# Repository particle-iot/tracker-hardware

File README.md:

# Tracker Hardware Resources

*Hardware repository for the Tracker SoM evaluation board and carrier board (Tracker One)*

Datasheets:

- [Tracker SoM](https://docs.particle.io/datasheets/asset-tracking/tracker-som-datasheet/)
- [Tracker SoM Evaluation Board](https://docs.particle.io/datasheets/asset-tracking/tracker-som-eval-board/)
- [Tracker One](https://docs.particle.io/datasheets/asset-tracking/tracker-one/)

In this repository you can find the following directories:

- eagle-eval: The Tracker SoM evaluation board
- eagle-carrier: The Tracker carrier board (the board in the Tracker One)

Within the Eagle directories are the standard Eagle files:

- *.sch Schematic file
- *.sch.pdf PDF version of the schematic (handy if you don't have Eagle CAD)
- *.brd Board Layout file
- *.lbr Library containing all of the components in the sch/brd files
- *.rar or *.zip Gerber files
- *.cam CAM file used to produce the Gerber file

The boards are identical for both Tracker SoM versions (T402 and T523).

Other useful resources include:

- [Creating your first Tracker SoM board tutorial](https://docs.particle.io/tutorials/asset-tracking/tracker-som-first-board/).

## Version History

### Tracker One (Carrier Board) v1.1 (2020-08-18)

1. Added TS3A5018 analog switch for isolate M8 IO pins.
2. Recalculated impedance, modified RF 50 ohm and USB 90 ohm trace width.
3. Added CAN BUS 5V output bypass fuse F2.

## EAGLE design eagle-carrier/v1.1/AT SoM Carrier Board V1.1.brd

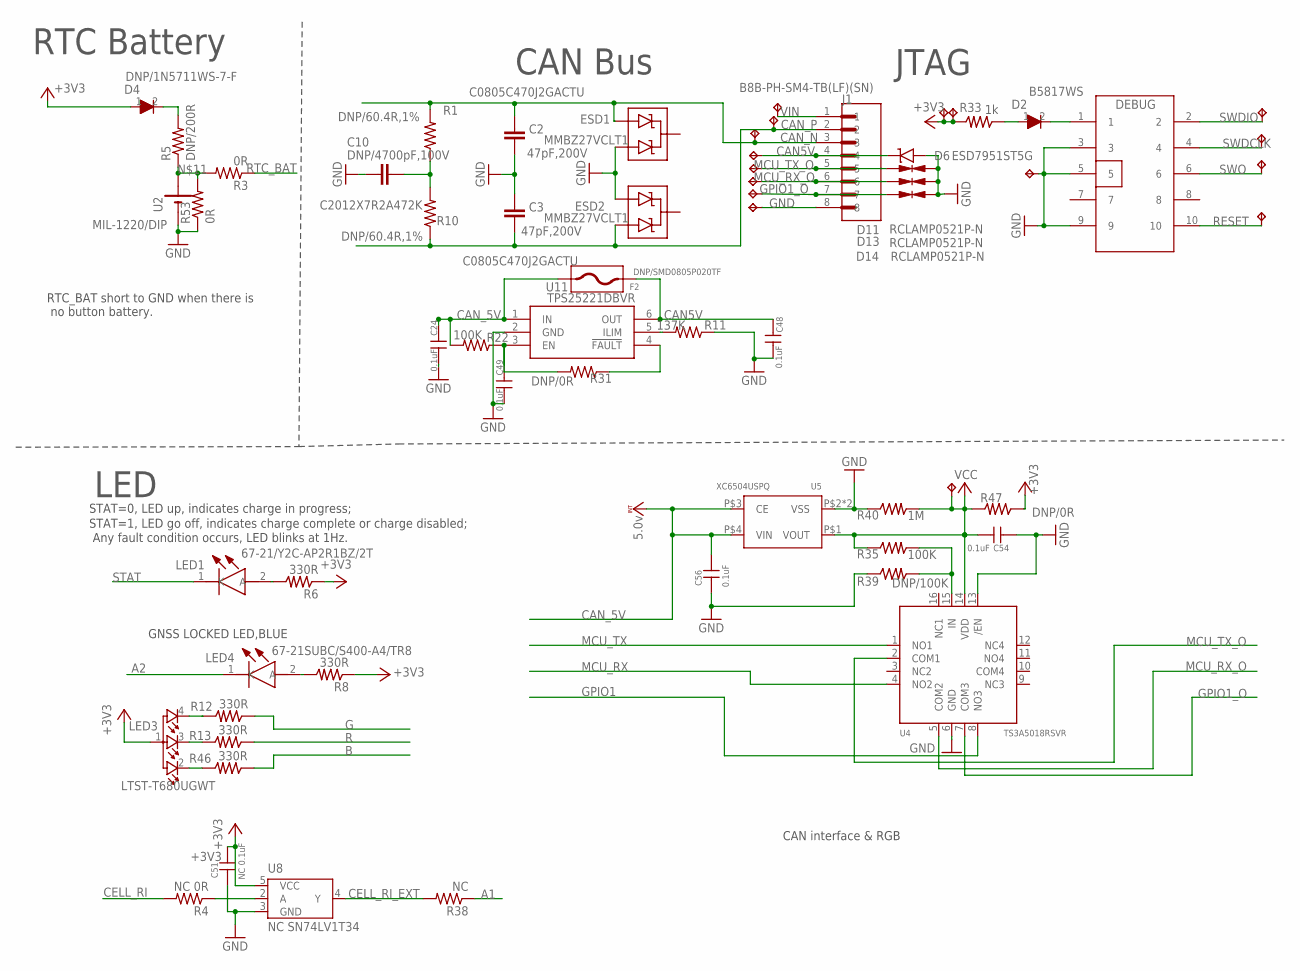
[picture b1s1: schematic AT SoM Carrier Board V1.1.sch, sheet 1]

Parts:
C2, C3: 47pF,200V; C0805; PART_NUMBER C0805C470J2GACTU
C10: DNP/4700pF,100V; C0805; PART_NUMBER C2012X7R2A472K
C24, C48, C49, C54, C56: 0.1uF; C-0402
C51: NC 0.1uF; C-0402
D2: B5817WS; SOD-323
D4: DNP/1N5711WS-7-F; SOD-323
D6: ESD7951ST5G; 0402-TVS-UNIDIR
D11, D13, D14: RCLAMP0521P-N; C0402
DEBUG: CON5X2; CON5X2_1.27
ESD1, ESD2: MMBZ27VCLT1; SOT23-3
F2: DNP/SMD0805P020TF; F0805
J1: B8B-PH-SM4-TB(LF)(SN); JST_B8B-PH-SM4-TB(LF)(SN)
LED1: 67-21/Y2C-AP2R1BZ/2T; LEDM3528X210N
LED3: LTST-T680UGWT; 150141M173100
LED4: 67-21SUBC/S400-A4/TR8; LEDM3528X210N
R1, R10: DNP/60.4R,1%; R1206
R3, R53: 0R; R0402_B
R4: NC 0R; R0402_B
R5: DNP/200R; R0402_B
R6, R8, R12, R13, R46: 330R; R-0402S
R11: 137K; R0402_B
R22: 100K; R0402_B
R31: DNP/0R; R0402_B
R33: 1k; R-0402S
R35: 100K; R-0402S
R38: NC; R0402_B
R39: DNP/100K; R-0402S
R40: 1M; R-0402S
R47: DNP/0R; R-0402S
TP11, TP12, TP13, TP15, TP16, TP21, TP22, TP43, TP44, TP46, TP47, TP48, TP49, TP50, TP51, TP52: TPTP10R; TP10R
U2: MIL-1220/DIP; BAT_ML-1220/DIP
U4: TS3A5018RSVR; UQFN-16
U5: XC6504USPQ; USPQ-4B04
U8: NC SN74LV1T34; SC70-5
U11: TPS25221DBVR; SOT95P280X145-6N

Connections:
+3V3: C51.1, D4.1, LED3.1, R6.1, R8.1, R33.2, R47.1, TP16.TP, TP21.TP, U8.5 (VCC); also elsewhere on the board
A1: R38.1; also elsewhere on the board
A2: LED4.1 (K); also elsewhere on the board
B: R46.1; also elsewhere on the board
CAN5V: C48.1, D6.1, F2.P$1 (1), J1.4, TP48.TP, U11.6 (OUT)
CAN_5V: C24.1, C56.1, F2.P$2 (2), R22.2, U5.P$3 (CE), U5.P$4 (VIN), U11.1 (IN); also elsewhere on the board
CAN_N: C2.1, ESD1.2 (A2), J1.3, R1.2, TP47.TP; also elsewhere on the board
CAN_P: C3.2, ESD2.1 (A1), J1.2, R10.1, TP46.TP; also elsewhere on the board
CELL_RI: R4.2; also elsewhere on the board
CELL_RI_EXT: R38.2, U8.4 (Y)
G: R12.1; also elsewhere on the board
GND: C2.2, C3.1, C10.1, C24.2, C48.2, C49.2, C51.2, C54.2, C56.2, D6.2, D11.2, D13.2, D14.2, DEBUG.3, DEBUG.5, DEBUG.9, ESD1.1 (A1), ESD2.2 (A2), J1.8, R11.1, R39.1, R40.1, R53.1, TP22.TP, TP52.TP, U2.1 (N), U4.6 (GND), U4.13 (/EN), U5.P$2 (VSS), U5.P$5 (VSS), U8.3 (GND), U11.2 (GND); also elsewhere on the board
GPIO1: U4.8 (NO3); also elsewhere on the board
GPIO1_O: D14.1, J1.7, TP51.TP, U4.7 (COM3)
MCU_RX: U4.4 (NO2); also elsewhere on the board
MCU_RX_O: D13.1, J1.6, TP50.TP, U4.5 (COM2)
MCU_TX: U4.1 (NO1); also elsewhere on the board
MCU_TX_O: D11.1, J1.5, TP49.TP, U4.2 (COM1)
unnamed: LED1.2 (A), R6.2
unnamed: LED4.2 (A), R8.2
unnamed: R4.1, U8.2 (A)
unnamed: D2.2, DEBUG.1
unnamed: C10.2, R1.1, R10.2
unnamed: R11.2, U11.5 (ILIM)
unnamed: R3.2, R5.1, R53.2, U2.2
unnamed: C49.1, R22.1, R31.2, U11.3 (EN)
unnamed: LED3.4, R12.2
unnamed: R31.1, U11.4 (!FAULT)
unnamed: D4.2, R5.2
unnamed: R35.2, R39.2, U4.15 (IN)
unnamed: LED3.2, R46.2
unnamed: LED3.3, R13.2
unnamed: D2.1, R33.1
R: R13.1; also elsewhere on the board
RESET: DEBUG.10, TP11.TP; also elsewhere on the board
RTC_BAT: R3.1; also elsewhere on the board
STAT: LED1.1 (K); also elsewhere on the board
SWDCLK: DEBUG.4, TP13.TP; also elsewhere on the board
SWDIO: DEBUG.2, TP15.TP; also elsewhere on the board
SWO: DEBUG.6, TP12.TP; also elsewhere on the board
VCC: C54.1, R35.1, R40.2, R47.2, TP44.TP, U4.14 (VDD), U5.P$1 (VOUT)
VIN: J1.1, TP43.TP; also elsewhere on the board

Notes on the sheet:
CAN Bus
LED
JTAG
RTC Battery
RTC_BAT short to GND when there is no button battery.
STAT=0, LED up, indicates charge in progress;
STAT=1, LED go off, indicates charge complete or charge disabled;
Any fault condition occurs, LED blinks at 1Hz.
GNSS LOCKED LED,BLUE
CAN interface & RGB

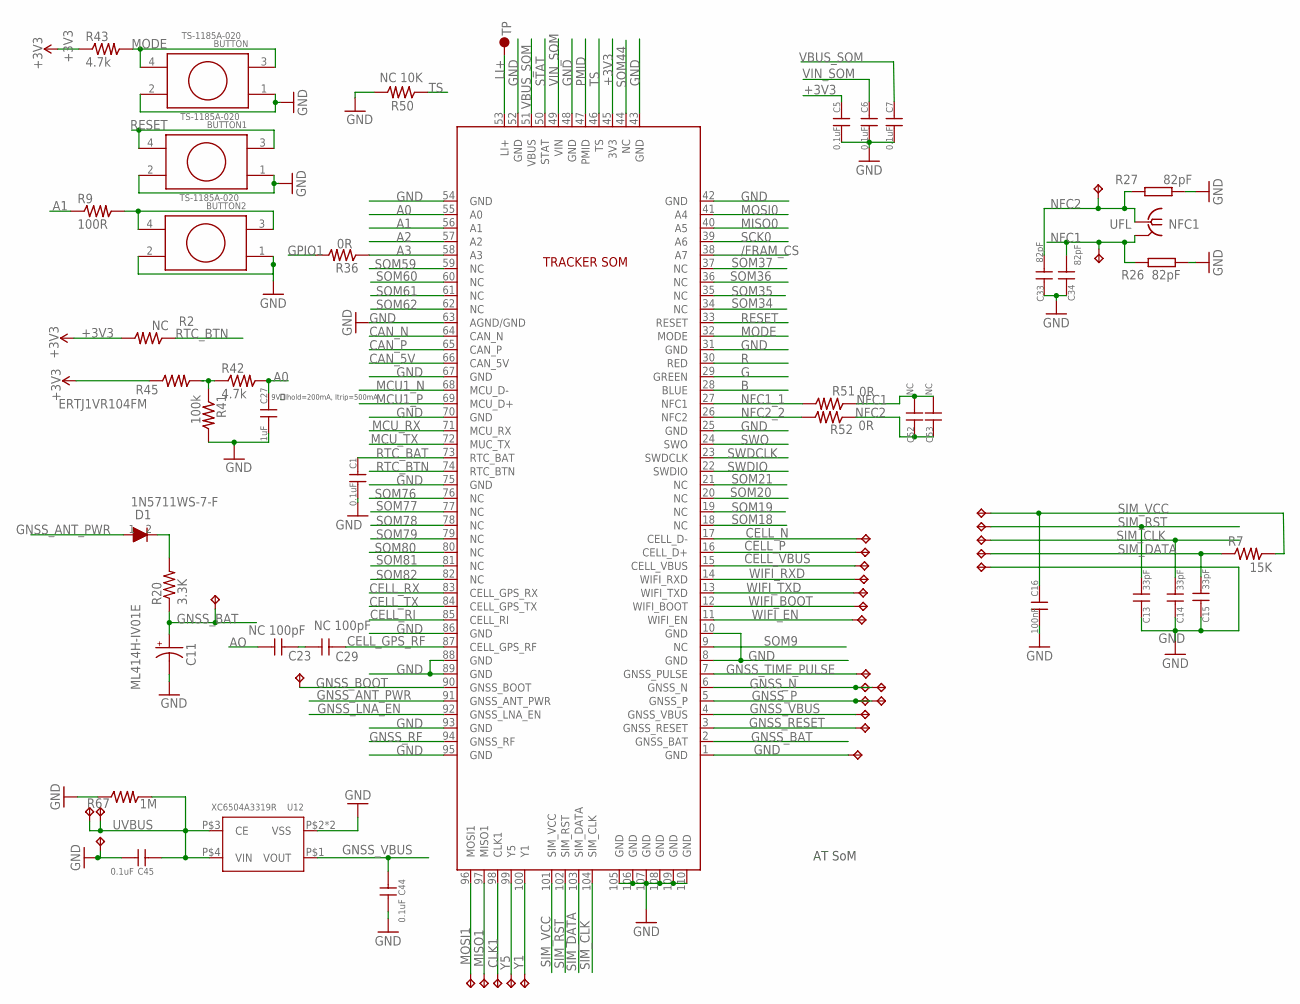
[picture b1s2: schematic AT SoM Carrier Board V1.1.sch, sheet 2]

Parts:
BUTTON, BUTTON1, BUTTON2: TS-1185A-020
C1, C5, C6, C7, C44, C45: 0.1uF; C-0402
C11: ML414H-IV01E; ML414H
C13, C14, C15: 33pF; C-0402
C16: 100nF; C-0402
C23, C29: NC 100pF; C0402_P
C27: 1uF; C-0402
C33, C34: 82pF; C-0402
C52, C53: NC; C-0402
D1: 1N5711WS-7-F; SOD-323
NFC1: UFL; IPEX-20279-001E
R2: NC; R-0402S
R7: 15K; R-0402S
R9: 100R; R-0402S
R20: 3.3K; R0603_P
R26, R27: 82pF; R-0402S
R36, R51, R52: 0R; R-0402S
R41: 100k; R-0402S
R42, R43: 4.7k; R-0402S
R45: ERTJ1VR104FM; R0603
R50: NC 10K; R-0402S
R67: 1M; R-0402S
TP1, TP2, TP3, TP4, TP5, TP6, TP7, TP8, TP9, TP14, TP17, TP18, TP19, TP20, TP27, TP28, TP29, TP30, TP31, TP32, TP33, TP34, TP35, TP36, TP37, TP38, TP39, TP40, TP41, TP42: TPTP10R; TP10R
U1: TRACKERSOM_V04
U12: XC6504A3319R; USPQ-4B04
U$1: TP2; TP70_BOT
U$9, U$10: TPTP10R; TP10R

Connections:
+3V3: C5.1, R2.2, R43.1, R45.1, U1.45 (3V3); also elsewhere on the board
/FRAM_CS: U1.38 (A7); also elsewhere on the board
A0: C27.1, R42.2, U1.55 (A0)
A1: R9.1, U1.56 (A1); also elsewhere on the board
A2: U1.57 (A2); also elsewhere on the board
A3: R36.1, U1.58 (A3)
AO: C23.1; also elsewhere on the board
B: U1.28 (BLUE); also elsewhere on the board
CAN_5V: U1.66 (CAN_5V); also elsewhere on the board
CAN_N: U1.64 (CAN_N); also elsewhere on the board
CAN_P: U1.65 (CAN_P); also elsewhere on the board
CELL_GPS_RF: C29.2, U1.87 (CELL_GPS_RF)
CELL_N: TP38.TP, U1.17 (CELL_D-)
CELL_P: TP36.TP, U1.16 (CELL_D+)
CELL_RI: U1.85 (CELL_RI); also elsewhere on the board
CELL_RX: U1.83 (CELL_GPS_RX)
CELL_TX: U1.84 (CELL_GPS_TX)
CELL_VBUS: TP35.TP, U1.15 (CELL_VBUS)
CLK1: TP40.TP, U1.98 (CLK1)
G: U1.29 (GREEN); also elsewhere on the board
GND: BUTTON.1, BUTTON.2, BUTTON1.1, BUTTON1.2, BUTTON2.1, BUTTON2.2, C1.2, C5.2, C6.2, C7.2, C11.-, C13.1, C14.1, C15.1, C16.2, C27.2, C33.1, C34.1, C44.1, C45.1, R26.2, R27.1, R41.2, R50.2, R67.1, TP18.TP, TP20.TP, TP32.TP, U1.1 (GND), U1.8 (GND), U1.10 (GND), U1.25 (GND), U1.31 (GND), U1.42 (GND), U1.43 (GND), U1.48 (GND), U1.52 (GND), U1.54 (GND), U1.63 (AGND/GND), U1.67 (GND), U1.70 (GND), U1.75 (GND), U1.86 (GND), U1.88 (GND), U1.89 (GND), U1.93 (GND), U1.95 (GND), U1.105 (GND), U1.106 (GND), U1.107 (GND), U1.108 (GND), U1.109 (GND), U1.110 (GND), U12.P$2 (VSS), U12.P$5 (VSS); also elsewhere on the board
GNSS_ANT_PWR: D1.1, U1.91 (GNSS_ANT_PWR); also elsewhere on the board
GNSS_BAT: C11.+, R20.1, TP9.TP, U1.2 (GNSS_BAT)
GNSS_BOOT: TP6.TP, U1.90 (GNSS_BOOT)
GNSS_LNA_EN: U1.92 (GNSS_LNA_EN); also elsewhere on the board
GNSS_N: TP14.TP, TP34.TP, U1.6 (GNSS_N); also elsewhere on the board
GNSS_P: TP5.TP, TP19.TP, U1.5 (GNSS_P); also elsewhere on the board
GNSS_RESET: TP8.TP, U1.3 (GNSS_RESET)
GNSS_RF: U1.94 (GNSS_RF); also elsewhere on the board
GNSS_TIME_PULSE: TP7.TP, U1.7 (GNSS_PULSE)
GNSS_VBUS: C44.2, TP30.TP, U1.4 (GNSS_VBUS), U12.P$1 (VOUT)
GPIO1: R36.2; also elsewhere on the board
LI+: U1.53 (LI+), U$1.P$1; also elsewhere on the board
MCU1_N: U1.68 (MCU_D-); also elsewhere on the board
MCU1_P: U1.69 (MCU_D+); also elsewhere on the board
MCU_RX: U1.71 (MCU_RX); also elsewhere on the board
MCU_TX: U1.72 (MUC_TX); also elsewhere on the board
MISO0: U1.40 (A5); also elsewhere on the board
MISO1: TP39.TP, U1.97 (MISO1)
MODE: BUTTON.3, BUTTON.4, R43.2, U1.32 (MODE)
MOSI0: U1.41 (A4); also elsewhere on the board
MOSI1: TP37.TP, U1.96 (MOSI1)
unnamed: R41.1, R42.1, R45.2
unnamed: D1.2, R20.2
unnamed: C23.2, C29.1
unnamed: BUTTON2.3, BUTTON2.4, R9.2
NFC1: C34.2, C52.2, C53.2, NFC1.2@1 (GND), NFC1.2@2 (GND), R26.1, R51.1, U$10.TP
NFC1_1: R51.2, U1.27 (NFC1)
NFC2: C33.2, C52.1, C53.1, NFC1.1, R27.2, R52.1, U$9.TP
NFC2_2: R52.2, U1.26 (NFC2)
PMID: U1.47 (PMID)
R: U1.30 (RED); also elsewhere on the board
RESET: BUTTON1.3, BUTTON1.4, U1.33 (RESET); also elsewhere on the board
RTC_BAT: C1.1, U1.73 (RTC_BAT); also elsewhere on the board
RTC_BTN: R2.1, U1.74 (RTC_BTN)
SCK0: U1.39 (A6); also elsewhere on the board
SIM_CLK: C14.2, TP29.TP, U1.104 (SIM_CLK)
SIM_DATA: C15.2, R7.1, TP31.TP, U1.103 (SIM_DATA)
SIM_RST: C13.2, TP28.TP, U1.102 (SIM_RST)
SIM_VCC: C16.1, R7.2, TP27.TP, U1.101 (SIM_VCC)
SOM9: U1.9 (NC)
SOM18: U1.18 (NC)
SOM19: U1.19 (NC)
SOM20: U1.20 (NC)
SOM21: U1.21 (NC)
SOM34: U1.34 (NC)
SOM35: U1.35 (NC)
SOM36: U1.36 (NC)
SOM37: U1.37 (NC)
SOM44: U1.44 (NC)
SOM59: U1.59 (NC)
SOM60: U1.60 (NC)
SOM61: U1.61 (NC)
SOM62: U1.62 (NC)
SOM76: U1.76 (NC)
SOM77: U1.77 (NC)
SOM78: U1.78 (NC)
SOM79: U1.79 (NC)
SOM80: U1.80 (NC)
SOM81: U1.81 (NC)
SOM82: U1.82 (NC)
STAT: U1.50 (STAT); also elsewhere on the board
SWDCLK: U1.23 (SWDCLK); also elsewhere on the board
SWDIO: U1.22 (SWDIO); also elsewhere on the board
SWO: U1.24 (SWO); also elsewhere on the board
TS: R50.1, U1.46 (TS)
UVBUS: C45.2, R67.2, TP17.TP, TP33.TP, U12.P$3 (CE), U12.P$4 (VIN); also elsewhere on the board
VBUS_SOM: C7.1, U1.51 (VBUS); also elsewhere on the board
VIN_SOM: C6.1, U1.49 (VIN); also elsewhere on the board
WIFI_BOOT: TP3.TP, U1.12 (WIFI_BOOT)
WIFI_EN: TP4.TP, U1.11 (WIFI_EN)
WIFI_RXD: TP1.TP, U1.14 (WIFI_RXD)
WIFI_TXD: TP2.TP, U1.13 (WIFI_TXD)
Y1: TP42.TP, U1.100 (Y1)
Y5: TP41.TP, U1.99 (Y5)

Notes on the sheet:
AT SoM
9V，Ihold=200mA, Itrip=500mA

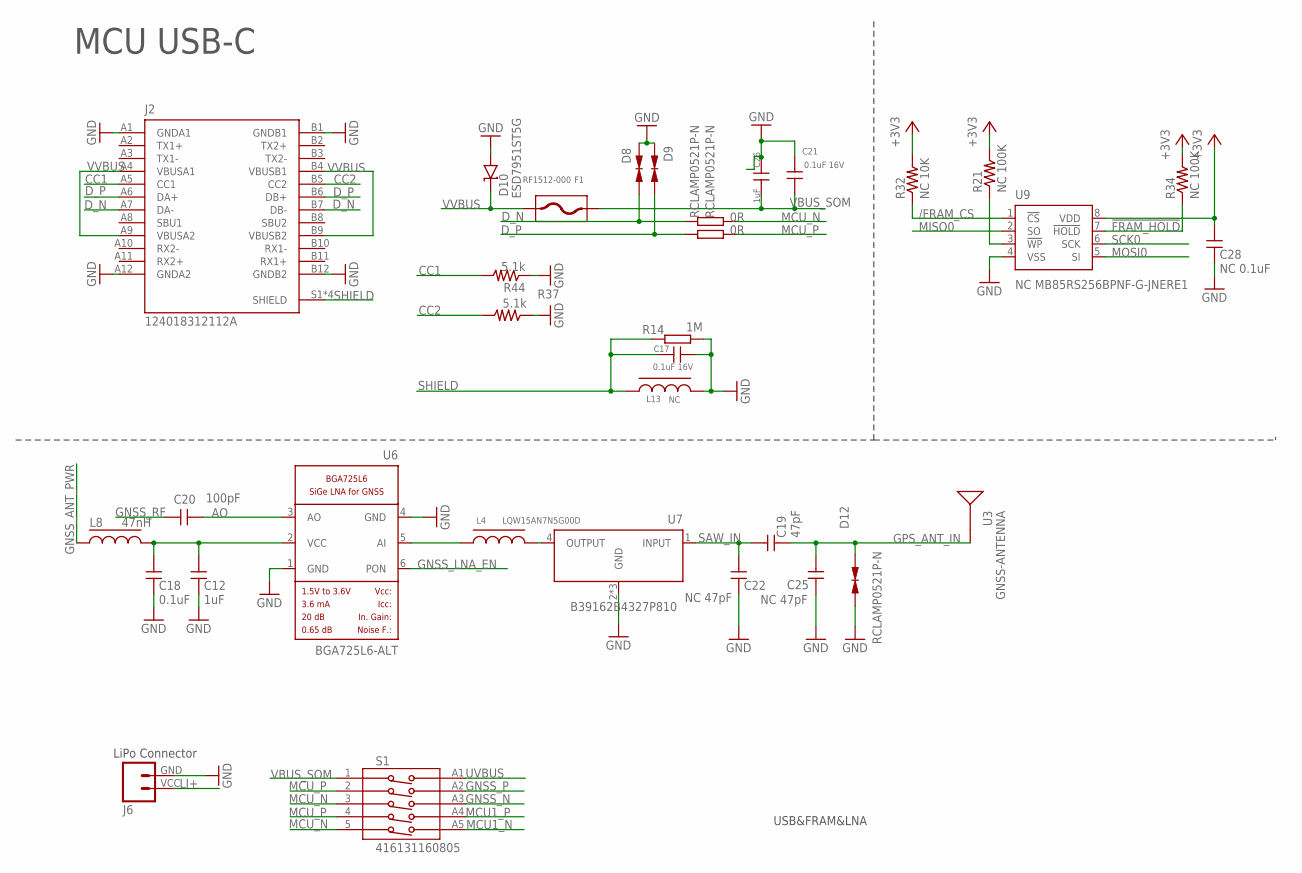
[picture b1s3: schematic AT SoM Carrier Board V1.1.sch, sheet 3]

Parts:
C12: 1uF; C0402_P
C17: 0.1uF 16V; PARTICLE-SZ_C-0402
C18: 0.1uF; C0402_P
C19: 47pF; C0402_P
C20: 100pF; C0402_P
C21: 0.1uF 16V; C-0402
C22, C25: NC 47pF; C0402_P
C26: 1uF; C-0402
C28: NC 0.1uF; C0402_P
D8, D9, D12: RCLAMP0521P-N; C0402
D10: ESD7951ST5G; 0402-TVS-UNIDIR
F1: RF1512-000; R1206
J2: 124018312112A; AMPHENOL_124018312112A
J6: M024UCON-15767; JST-2-SMD-VERT
L4: LQW15AN7N5G00D; R-0402S
L8: 47nH; R-0402S
L13: NC; R-0603A
R14: 1M; REDBEAR_R0603
R15, R16: 0R; R-0402S
R21, R34: NC 100K; R-0402S
R32: NC 10K; R-0402S
R37, R44: 5.1k; R-0402S
S1: 416131160805
U3: GNSS-ANTENNA; PA035AZ0004
U6: BGA725L6-ALT; LNA-TSLP-6-2-ALT
U7: B39162B4327P810; QCS5I
U9: NC MB85RS256BPNF-G-JNERE1; SO08

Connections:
!FRAM_HOLD: R34.1, U9.7 (!HOLD)
!FRAM_WP: R21.1, U9.3 (!WP)
+3V3: C28.1, R21.2, R32.2, R34.2, U9.8 (VDD); also elsewhere on the board
/FRAM_CS: R32.1, U9.1 (!CS); also elsewhere on the board
AO: C20.2, U6.3 (AO); also elsewhere on the board
CC1: J2.A5 (CC1), R44.2
CC2: J2.B5 (CC2), R37.2
D_N: D8.2, J2.A7 (DA-), J2.B7 (DB-), R15.1
D_P: D9.2, J2.A6 (DA+), J2.B6 (DB+), R16.1
GND: C12.2, C17.2, C18.2, C21.2, C22.2, C25.1, C26.1, C28.2, D8.1, D9.1, D10.2, D12.2, J2.A1 (GNDA1), J2.A12 (GNDA2), J2.B1 (GNDB1), J2.B12 (GNDB2), J6.GND (1), L13.2, R14.2, R37.1, R44.1, U6.1 (GND), U6.4 (GND), U7.2 (GND), U7.3 (GND), U7.5 (GND), U9.4 (VSS); also elsewhere on the board
GNSS_ANT_PWR: L8.1; also elsewhere on the board
GNSS_LNA_EN: U6.6 (PON); also elsewhere on the board
GNSS_N: S1.A3; also elsewhere on the board
GNSS_P: S1.A2; also elsewhere on the board
GNSS_RF: C20.1; also elsewhere on the board
GPS_ANT_IN: C19.2, C25.2, D12.1, U3.P$1
LI+: J6.VCC (2); also elsewhere on the board
MCU1_N: S1.A5; also elsewhere on the board
MCU1_P: S1.A4; also elsewhere on the board
MCU_N: R15.2, S1.3, S1.5
MCU_P: R16.2, S1.2, S1.4
MISO0: U9.2 (SO); also elsewhere on the board
MOSI0: U9.5 (SI); also elsewhere on the board
unnamed: L4.2, U7.4 (OUTPUT)
unnamed: L4.1, U6.5 (AI)
unnamed: C12.1, C18.1, L8.2, U6.2 (VCC)
SAW_IN: C19.1, C22.1, U7.1 (INPUT)
SCK0: U9.6 (SCK); also elsewhere on the board
SHIELD: C17.1, J2.S1 (SHIELD), J2.S2 (SHIELD), J2.S3 (SHIELD), J2.S4 (SHIELD), L13.1, R14.1
UVBUS: S1.A1; also elsewhere on the board
VBUS_SOM: C21.1, C26.2, F1.2, S1.1; also elsewhere on the board
VVBUS: D10.1, F1.1, J2.A4 (VBUSA1), J2.A9 (VBUSA2), J2.B4 (VBUSB1), J2.B9 (VBUSB2)

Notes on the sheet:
MCU USB-C
USB&FRAM&LNA
LiPo Connector

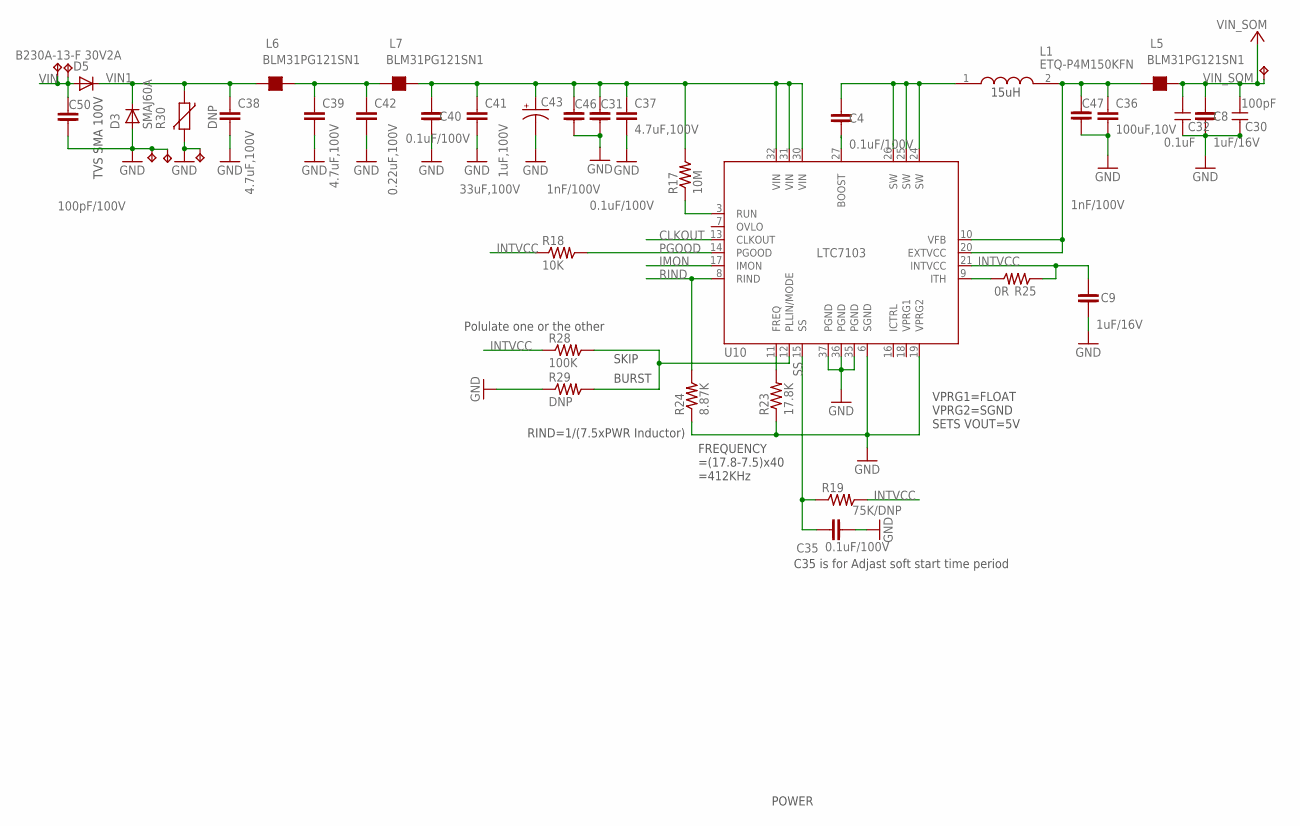
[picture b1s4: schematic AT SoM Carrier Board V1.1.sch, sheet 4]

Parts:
C4, C31, C35, C40: 0.1uF/100V; C-0603A
C8, C9: 1uF/16V; C-0402
C30: 100pF; C0402_P
C32: 0.1uF; C0402_P
C36: 100uF,10V; C1210
C37, C38, C39: 4.7uF,100V; C1210
C41: 1uF,100V; C0805
C42: 0.22uF,100V; C0805
C43: 33uF,100V; NIC_10X10.5_CAP
C46, C47: 1nF/100V; C-0603A
C50: 100pF/100V; C-0603A
D3: SMAJ60A; SMADIODE
D5: B230A-13-F 30V2A; SMADIODE
L1: ETQ-P4M150KFN; ETQP4M150KFN
L5, L6, L7: BLM31PG121SN1; L1206
R17: 10M; R-0402S
R18: 10K; R-0402S
R19: 75K/DNP; R-0402S
R23: 17.8K; R0603_P
R24: 8.87K; R-0402S
R25: 0R; R-0402S
R28: 100K; R-0402S
R29: DNP; R-0402S
R30: DNP; R-5
TP10, TP23, TP24, TP25, TP26, TP45: TPTP10R; TP10R
U10: LTC7103; UHE36(26)QFN

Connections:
CLKOUT: U10.13 (CLKOUT)
GND: C8.2, C9.2, C30.2, C31.2, C32.2, C35.2, C36.2, C37.2, C38.2, C39.2, C40.2, C41.2, C42.2, C43.-, C46.2, C47.2, C50.2, D3.A, R23.1, R24.1, R29.1, R30.2, TP24.TP, TP25.TP, TP26.TP, U10.6 (SGND), U10.19 (VPRG2), U10.35 (PGND), U10.36 (PGND), U10.37 (PGND); also elsewhere on the board
IMON: U10.17 (IMON)
INTVCC: C9.1, R18.1, R19.2, R25.1, R28.1, U10.21 (INTVCC)
unnamed: C4.2, U10.27 (BOOST)
unnamed: C36.1, C47.1, L1.2, L5.1, U10.10 (VFB), U10.20 (EXTVCC)
unnamed: C4.1, L1.1, U10.24 (SW), U10.25 (SW), U10.26 (SW)
unnamed: C39.1, C42.1, L6.2, L7.1
unnamed: R17.1, U10.3 (RUN)
unnamed: R23.2, U10.11 (FREQ)
unnamed: R28.2, R29.2, U10.12 (PLLIN/MODE)
unnamed: R25.2, U10.9 (ITH)
unnamed: C31.1, C37.1, C40.1, C41.1, C43.+, C46.1, L7.2, R17.2, U10.30 (VIN), U10.31 (VIN), U10.32 (VIN)
PGOOD: R18.2, U10.14 (PGOOD)
RIND: R24.2, U10.8 (RIND)
SS: C35.1, R19.1, U10.15 (SS)
VIN: C50.1, D5.A, TP23.TP, TP45.TP; also elsewhere on the board
VIN1: C38.1, D3.C, D5.C, L6.1, R30.1
VIN_SOM: C8.1, C30.1, C32.1, L5.2, TP10.TP; also elsewhere on the board

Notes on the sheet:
VPRG1=FLOAT VPRG2=SGND SETS VOUT=5V
FREQUENCY =(17.8-7.5)x40 =412KHz
RIND=1/(7.5xPWR Inductor)
Polulate one or the other
SKIP
BURST
15uH
TVS SMA 100V
POWER
C35 is for Adjast soft start time period

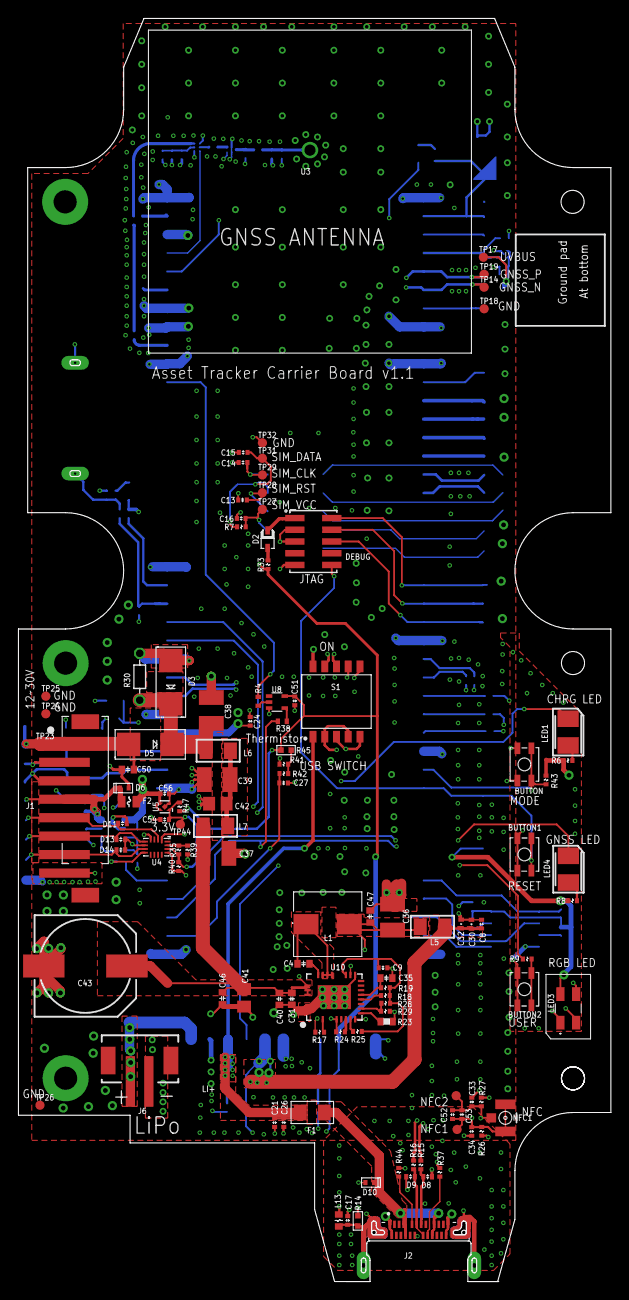
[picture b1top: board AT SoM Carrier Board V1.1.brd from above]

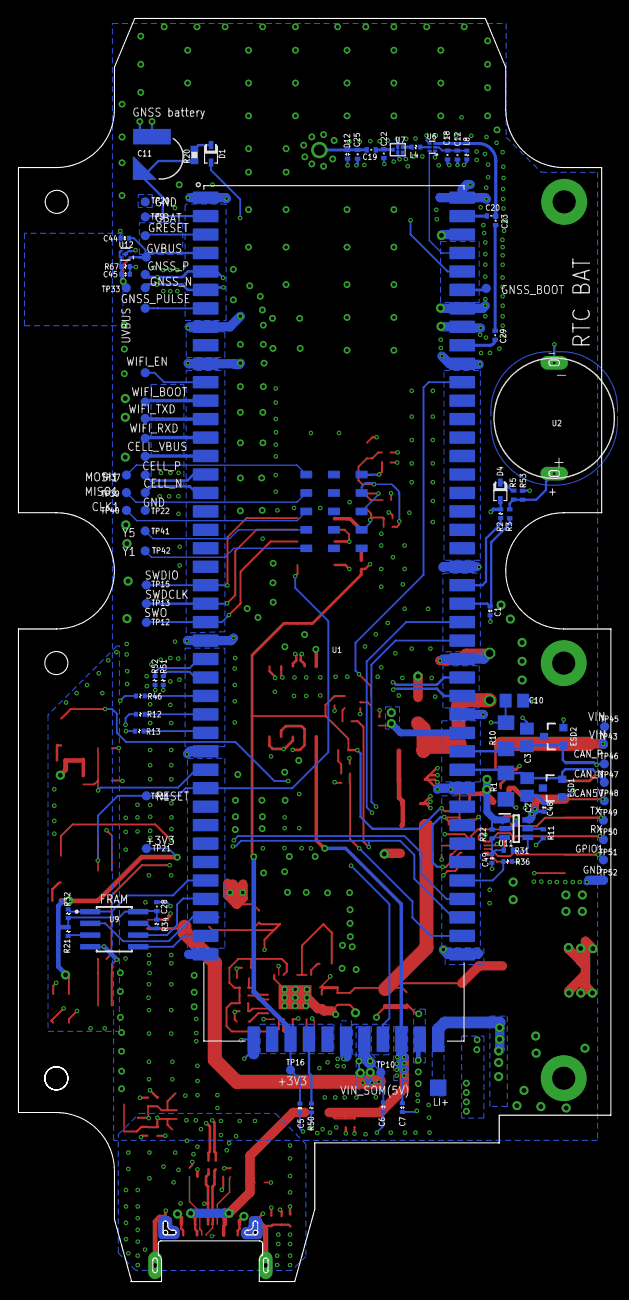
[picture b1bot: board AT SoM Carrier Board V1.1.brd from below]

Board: 4 copper layers, 64.2 x 136.9 mm, 210 parts (94 on the bottom side), 122 nets.

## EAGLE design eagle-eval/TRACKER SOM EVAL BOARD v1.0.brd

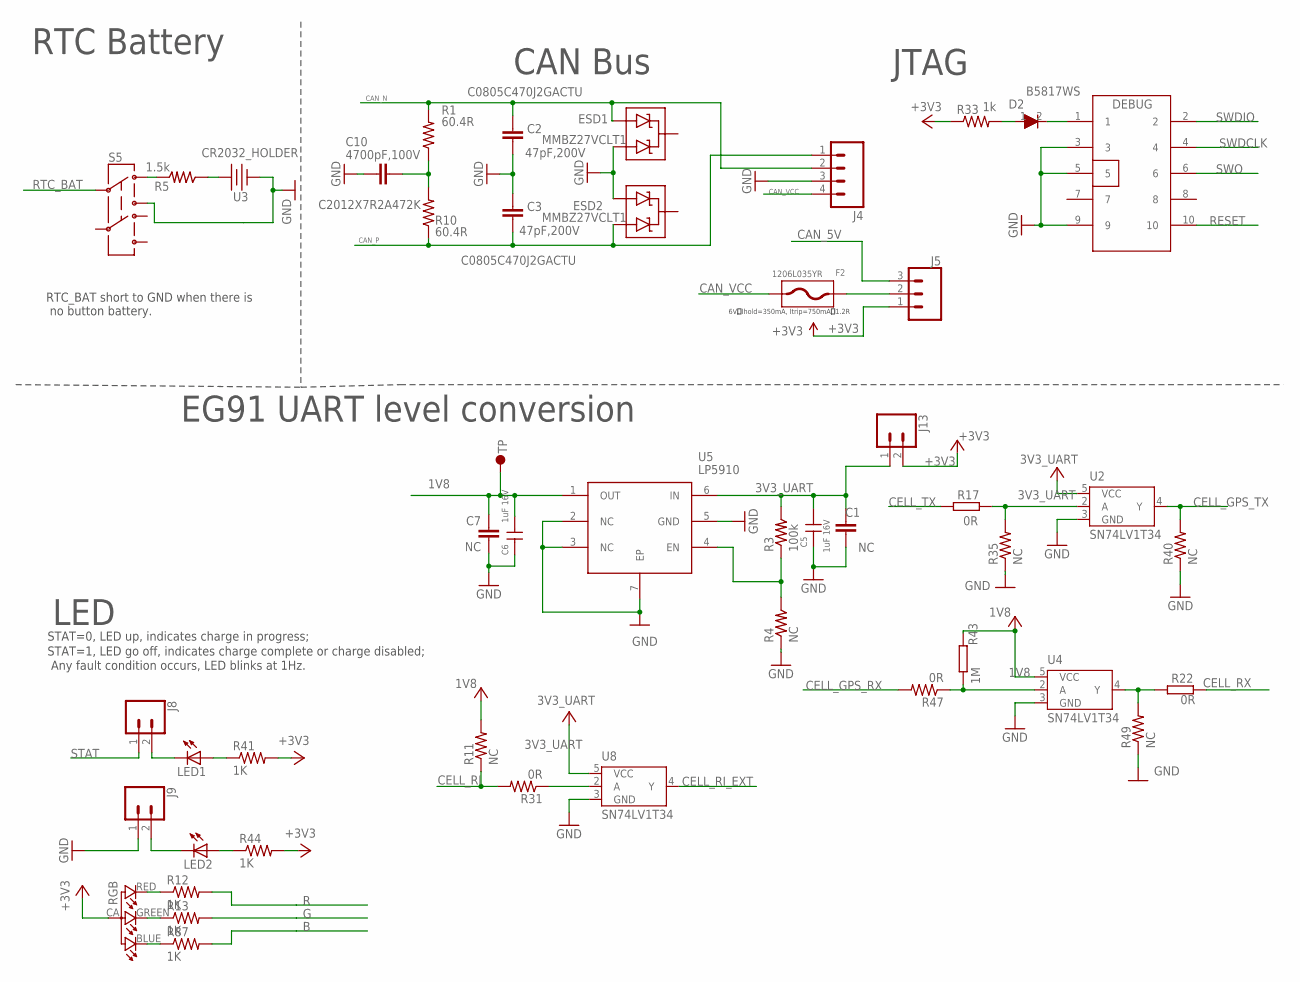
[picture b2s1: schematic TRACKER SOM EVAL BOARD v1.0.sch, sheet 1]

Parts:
C1, C7: NC; C0805
C2, C3: 47pF,200V; C0805; PART_NUMBER C0805C470J2GACTU
C5, C6: 1uF 16V; C0603
C10: 4700pF,100V; C0805; PART_NUMBER C2012X7R2A472K
D2: B5817WS; SOD-323
DEBUG: CON 2X5P; CON5X2_1.27
ESD1, ESD2: MMBZ27VCLT1; SOT23-3
F2: 1206L035YR; R1206
J4: M04SCREW; SCREWTERMINAL-3.5MM-4; PARTNO OSTTE040104
J5: CONN_03_2.54MM; 1X03
J8, J9, J13: CONN_02; 1X02
LED1, LED2: LED0603; LED-0603
R1, R10: 60.4R; R1206
R3: 100k; R-0402S
R4: NC; R-0402S
R5: 1.5k; R-0402S
R11, R35, R40, R49: NC; R0402_B
R12, R13, R41, R44, R87: 1K; R0603
R17, R22: 0R; R0603
R31, R47: 0R; R0402_B
R33: 1k; 0603
R43: 1M; REDBEAR_R0603
RGB: RGB-LED-CLMVB-FKARGB; PLCC4-2MM-RGB
S5: SWITCH-DPDT; SWITCH-2.5X3.2-6
U2, U4, U8: SN74LV1T34; SC70-5
U3: CR2032_HOLDER
U5: LP5910; QFN6P
U$4: TP5; TP30_TOP

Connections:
1V8: C6.1, C7.1, R11.2, R43.1, U4.5 (VCC), U5.1 (OUT), U$4.P$1
3V3_UART: C1.1, C5.1, J13.1, R3.2, U2.5 (VCC), U5.6 (IN), U8.5 (VCC)
+3V3: J5.1, J13.2, R33.1, R41.2, R44.2, RGB.CA (1); also elsewhere on the board
B: R87.2; also elsewhere on the board
CAN_5V: J5.3; also elsewhere on the board
CAN_N: C2.1, ESD1.2 (A2), J4.2, R1.2; also elsewhere on the board
CAN_P: C3.2, ESD2.1 (A1), J4.1, R10.1; also elsewhere on the board
CAN_VCC: F2.1, J4.4
CELL_GPS_RX: R47.2; also elsewhere on the board
CELL_GPS_TX: R40.2, U2.4 (Y); also elsewhere on the board
CELL_RI: R11.1, R31.2; also elsewhere on the board
CELL_RI_EXT: U8.4 (Y); also elsewhere on the board
CELL_RX: R22.1; also elsewhere on the board
CELL_TX: R17.2; also elsewhere on the board
G: R13.2; also elsewhere on the board
GND: C1.2, C2.2, C3.1, C5.2, C6.2, C7.2, C10.1, DEBUG.3, DEBUG.5, DEBUG.9, ESD1.1 (A1), ESD2.2 (A2), J4.3, J9.1, R4.1, R35.1, R40.1, R49.1, S5.3, U2.3 (GND), U3.-, U4.3 (GND), U5.2 (NC), U5.3 (NC), U5.5 (GND), U5.7 (EP), U8.3 (GND); also elsewhere on the board
unnamed: LED1.A, R41.1
unnamed: J8.2, LED1.C
unnamed: LED2.A, R44.1
unnamed: J9.2, LED2.C
unnamed: C10.2, R1.1, R10.2
unnamed: R17.1, R35.2, U2.2 (A)
unnamed: R31.1, U8.2 (A)
unnamed: R3.1, R4.2, U5.4 (EN)
unnamed: R5.2, S5.1
unnamed: R12.1, RGB.RED (4)
unnamed: R43.2, R47.1, U4.2 (A)
unnamed: F2.2, J5.2
unnamed: R22.2, R49.2, U4.4 (Y)
unnamed: R87.1, RGB.BLUE (2)
unnamed: R13.1, RGB.GREEN (3)
unnamed: R5.1, U3.+
unnamed: D2.1, R33.2
unnamed: D2.2, DEBUG.1
R: R12.2; also elsewhere on the board
RESET: DEBUG.10; also elsewhere on the board
RTC_BAT: S5.2; also elsewhere on the board
STAT: J8.1; also elsewhere on the board
SWDCLK: DEBUG.4; also elsewhere on the board
SWDIO: DEBUG.2; also elsewhere on the board
SWO: DEBUG.6; also elsewhere on the board

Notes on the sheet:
CAN Bus
EG91 UART level conversion
LED
JTAG
RTC Battery
RTC_BAT short to GND when there is no button battery.
STAT=0, LED up, indicates charge in progress;
STAT=1, LED go off, indicates charge complete or charge disabled;
Any fault condition occurs, LED blinks at 1Hz.
6V，Ihold=350mA, Itrip=750mA，1.2R

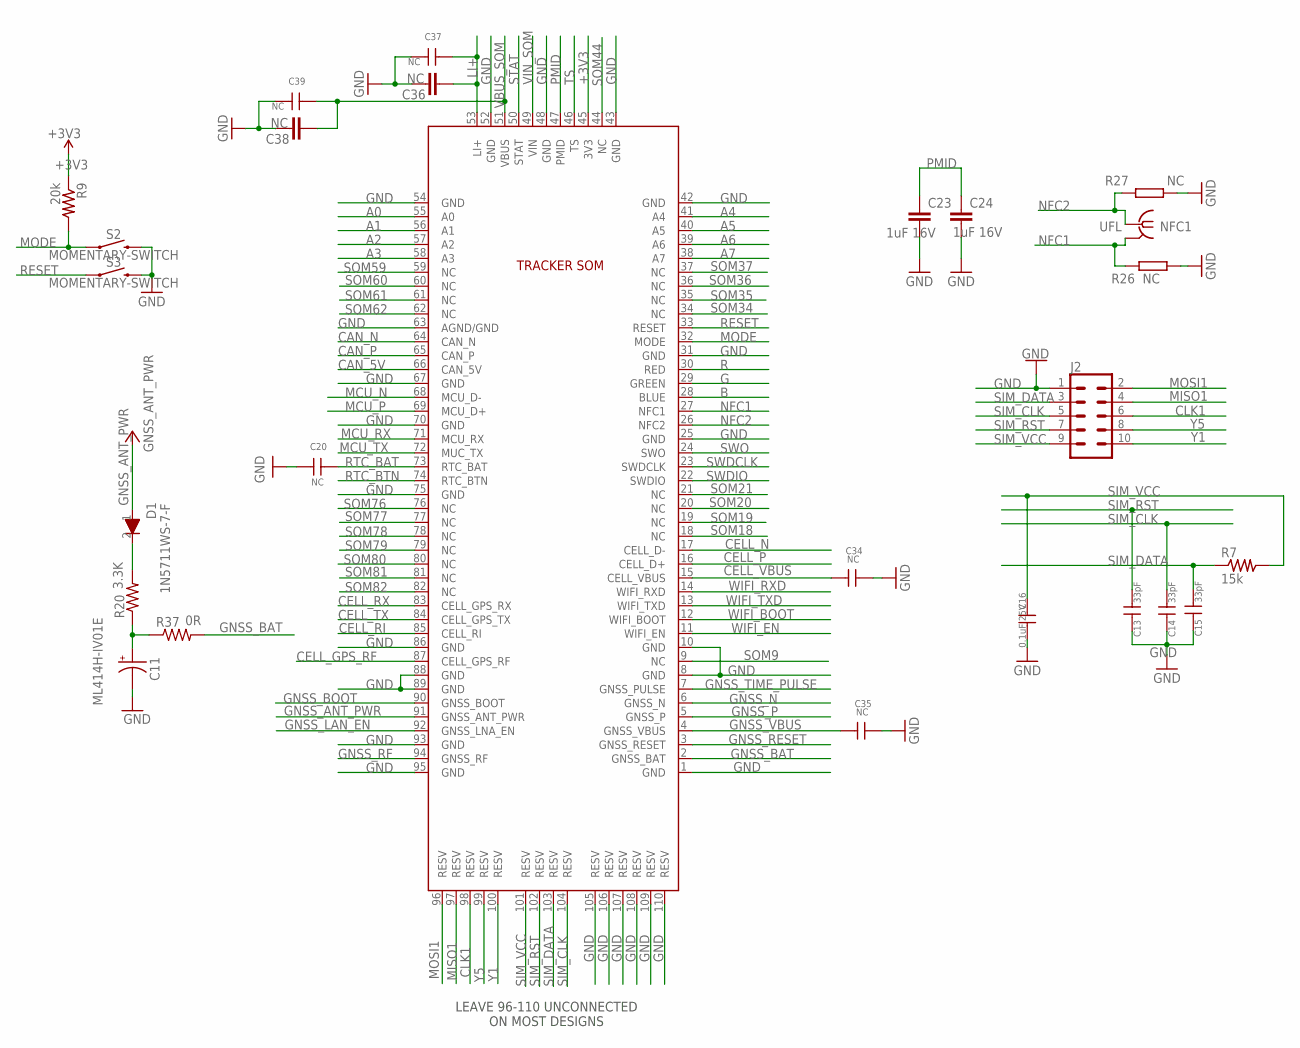
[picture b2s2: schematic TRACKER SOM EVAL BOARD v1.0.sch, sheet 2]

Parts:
C11: ML414H-IV01E; ML414H
C13, C14, C15: 33pF; C-0402
C16: 0.1uF 25V; C-0402
C20, C34, C35, C37, C39: NC; C-0402
C23, C24: 1uF 16V; C0805
C36, C38: NC; C1206
D1: 1N5711WS-7-F; SOD-323
J2: CONN_05X2PTH; 2X5
NFC1: UFL; IPEX-20279-001E
R7: 15k; R-0402S
R9: 20k; R-0402S
R20: 3.3K; 0603
R26, R27: NC; R-0402S
R37: 0R; 0603
S2, S3: MOMENTARY-SWITCH; TACTILE_SWITCH_PTH_6.0MM
U1: TRACKER-SOM-3A

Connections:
+3V3: R9.1, U1.45 (3V3); also elsewhere on the board
A0: U1.55 (A0); also elsewhere on the board
A1: U1.56 (A1); also elsewhere on the board
A2: U1.57 (A2); also elsewhere on the board
A3: U1.58 (A3); also elsewhere on the board
A4: U1.41 (A4); also elsewhere on the board
A5: U1.40 (A5); also elsewhere on the board
A6: U1.39 (A6); also elsewhere on the board
A7: U1.38 (A7); also elsewhere on the board
B: U1.28 (BLUE); also elsewhere on the board
CAN_5V: U1.66 (CAN_5V); also elsewhere on the board
CAN_N: U1.64 (CAN_N); also elsewhere on the board
CAN_P: U1.65 (CAN_P); also elsewhere on the board
CELL_GPS_RF: U1.87 (CELL_GPS_RF)
CELL_N: U1.17 (CELL_D-); also elsewhere on the board
CELL_P: U1.16 (CELL_D+); also elsewhere on the board
CELL_RI: U1.85 (CELL_RI); also elsewhere on the board
CELL_RX: U1.83 (CELL_GPS_RX); also elsewhere on the board
CELL_TX: U1.84 (CELL_GPS_TX); also elsewhere on the board
CELL_VBUS: C34.2, U1.15 (CELL_VBUS); also elsewhere on the board
CLK1: J2.6, U1.98 (RESV)
G: U1.29 (GREEN); also elsewhere on the board
GND: C11.-, C13.1, C14.1, C15.1, C16.2, C20.1, C23.2, C24.2, C34.1, C35.1, C36.1, C37.1, C38.1, C39.1, J2.1, R26.2, R27.1, S2.3 (2), S3.3 (2), U1.1 (GND), U1.8 (GND), U1.10 (GND), U1.25 (GND), U1.31 (GND), U1.42 (GND), U1.43 (GND), U1.48 (GND), U1.52 (GND), U1.54 (GND), U1.63 (AGND/GND), U1.67 (GND), U1.70 (GND), U1.75 (GND), U1.86 (GND), U1.88 (GND), U1.89 (GND), U1.93 (GND), U1.95 (GND), U1.105 (RESV), U1.106 (RESV), U1.107 (RESV), U1.108 (RESV), U1.109 (RESV), U1.110 (RESV); also elsewhere on the board
GNSS_ANT_PWR: D1.1, U1.91 (GNSS_ANT_PWR)
GNSS_BAT: R37.2, U1.2 (GNSS_BAT)
GNSS_BOOT: U1.90 (GNSS_BOOT)
GNSS_LAN_EN: U1.92 (GNSS_LNA_EN)
GNSS_N: U1.6 (GNSS_N); also elsewhere on the board
GNSS_P: U1.5 (GNSS_P); also elsewhere on the board
GNSS_RESET: U1.3 (GNSS_RESET)
GNSS_RF: U1.94 (GNSS_RF)
GNSS_TIME_PULSE: U1.7 (GNSS_PULSE); also elsewhere on the board
GNSS_VBUS: C35.2, U1.4 (GNSS_VBUS); also elsewhere on the board
LI+: C36.2, C37.2, U1.53 (LI+); also elsewhere on the board
MCU_N: U1.68 (MCU_D-); also elsewhere on the board
MCU_P: U1.69 (MCU_D+); also elsewhere on the board
MCU_RX: U1.71 (MCU_RX); also elsewhere on the board
MCU_TX: U1.72 (MUC_TX); also elsewhere on the board
MISO1: J2.4, U1.97 (RESV)
MODE: R9.2, S2.1, U1.32 (MODE); also elsewhere on the board
MOSI1: J2.2, U1.96 (RESV)
unnamed: D1.2, R20.2
unnamed: C11.+, R20.1, R37.1
NFC1: NFC1.2@1 (GND), NFC1.2@2 (GND), R26.1, U1.27 (NFC1); also elsewhere on the board
NFC2: NFC1.1, R27.2, U1.26 (NFC2); also elsewhere on the board
PMID: C23.1, C24.1, U1.47 (PMID); also elsewhere on the board
R: U1.30 (RED); also elsewhere on the board
RESET: S3.1, U1.33 (RESET); also elsewhere on the board
RTC_BAT: C20.2, U1.73 (RTC_BAT); also elsewhere on the board
RTC_BTN: U1.74 (RTC_BTN); also elsewhere on the board
SIM_CLK: C14.2, J2.5, U1.104 (RESV)
SIM_DATA: C15.2, J2.3, R7.1, U1.103 (RESV)
SIM_RST: C13.2, J2.7, U1.102 (RESV)
SIM_VCC: C16.1, J2.9, R7.2, U1.101 (RESV)
SOM9: U1.9 (NC); also elsewhere on the board
SOM18: U1.18 (NC); also elsewhere on the board
SOM19: U1.19 (NC); also elsewhere on the board
SOM20: U1.20 (NC); also elsewhere on the board
SOM21: U1.21 (NC); also elsewhere on the board
SOM34: U1.34 (NC); also elsewhere on the board
SOM35: U1.35 (NC); also elsewhere on the board
SOM36: U1.36 (NC); also elsewhere on the board
SOM37: U1.37 (NC); also elsewhere on the board
SOM44: U1.44 (NC); also elsewhere on the board
SOM59: U1.59 (NC); also elsewhere on the board
SOM60: U1.60 (NC); also elsewhere on the board
SOM61: U1.61 (NC); also elsewhere on the board
SOM62: U1.62 (NC); also elsewhere on the board
SOM76: U1.76 (NC); also elsewhere on the board
SOM77: U1.77 (NC); also elsewhere on the board
SOM78: U1.78 (NC); also elsewhere on the board
SOM79: U1.79 (NC); also elsewhere on the board
SOM80: U1.80 (NC); also elsewhere on the board
SOM81: U1.81 (NC); also elsewhere on the board
SOM82: U1.82 (NC); also elsewhere on the board
STAT: U1.50 (STAT); also elsewhere on the board
SWDCLK: U1.23 (SWDCLK); also elsewhere on the board
SWDIO: U1.22 (SWDIO); also elsewhere on the board
SWO: U1.24 (SWO); also elsewhere on the board
TS: U1.46 (TS); also elsewhere on the board
VBUS_SOM: C38.2, C39.2, U1.51 (VBUS); also elsewhere on the board
VIN_SOM: U1.49 (VIN); also elsewhere on the board
WIFI_BOOT: U1.12 (WIFI_BOOT); also elsewhere on the board
WIFI_EN: U1.11 (WIFI_EN); also elsewhere on the board
WIFI_RXD: U1.14 (WIFI_RXD); also elsewhere on the board
WIFI_TXD: U1.13 (WIFI_TXD); also elsewhere on the board
Y1: J2.10, U1.100 (RESV)
Y5: J2.8, U1.99 (RESV)

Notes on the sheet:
LEAVE 96-110 UNCONNECTED ON MOST DESIGNS

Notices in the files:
parts and their libraries:
rc-master: Copyright (C) 2007, Bob Starr
SparkFun-Capacitors: Licensing: Creative Commons ShareAlike 4.0 International - https://creativecommons.org/licenses/by-sa/4.0
SparkFun-Aesthetics: Licensing: CC v3.0 Share-Alike You are welcome to use this library for commercial purposes.
